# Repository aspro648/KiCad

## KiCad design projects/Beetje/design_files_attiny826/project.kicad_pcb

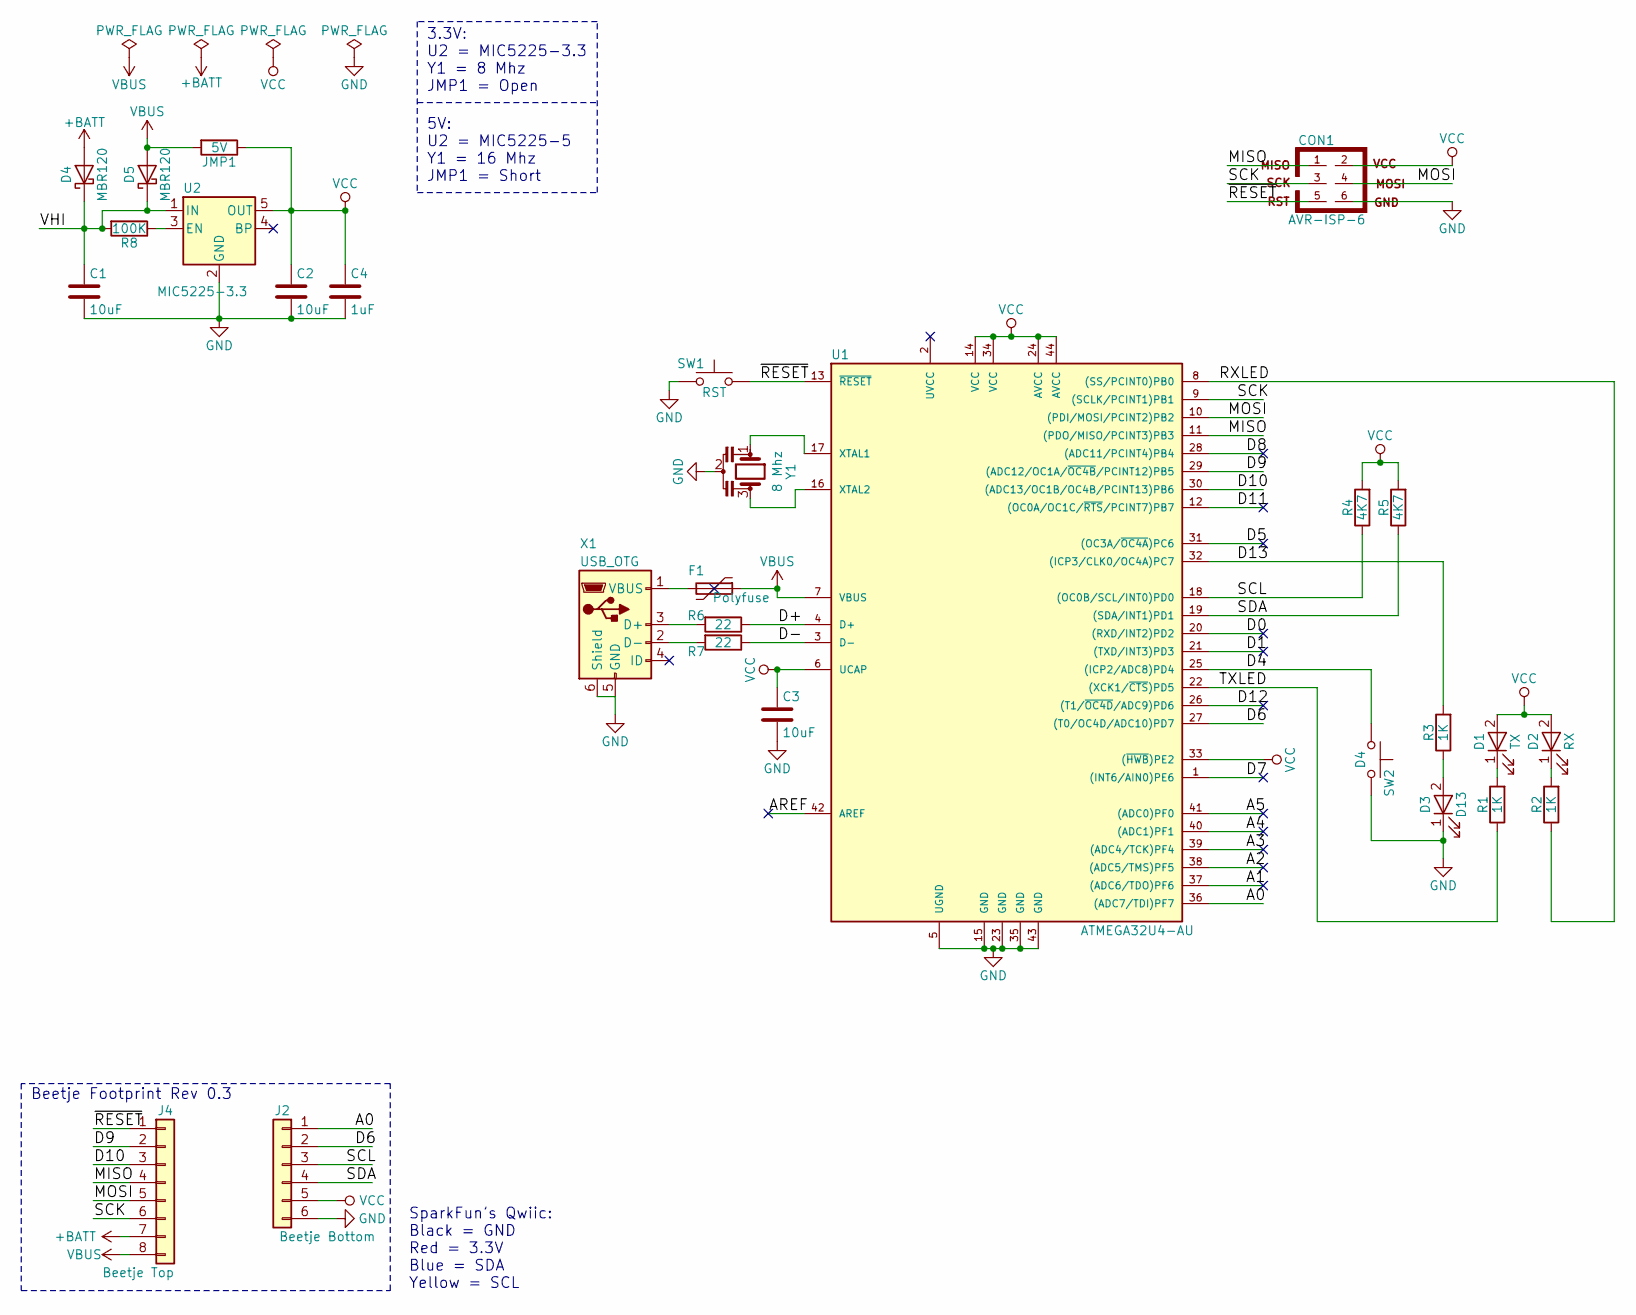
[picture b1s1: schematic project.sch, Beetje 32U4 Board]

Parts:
C1, C2, C3: 10uF; C_0805
C4: 1uF; C_0603
CON1: AVR-ISP-6; Pin_Header_Straight_2x03_Pitch2.54mm
D1: TX; LED_0603
D2: RX; LED_0603
D3: D13; LED_0603
D4, D5: MBR120; D_SOD-123F
F1: Polyfuse; R_1206
J2: Beetje Bottom; Beetje_Bottom
J4: Beetje Top; Beetje_Top
JMP1: 5V; Jumper
R1, R2, R3: 1K; R_0603
R4, R5: 4K7; R_0603
R6, R7: 22; R_0603
R8: 100K; R_0603
SW1: RST; EVQ-P7A
SW2: D4; EVQ-P7A
U1: ATMEGA32U4-AU; TQFP-44_10x10mm_Pitch0.8mm
U2: MIC5225-3.3; SOT-23-5
X1: USB_OTG; USB_Micro-B_Molex-105017-0001
Y1: 8 Mhz; Resonator_SMD_CTSC_1.3mmx3.2mm

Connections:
+BATT: D4.2 (A), J4.7
/A0: J2.1, U1.36 ((ADC7/TDI)PF7)
/A1: U1.37 ((ADC6/TDO)PF6)
/A2: U1.38 ((ADC5/TMS)PF5)
/A3: U1.39 ((ADC4/TCK)PF4)
/A4: U1.40 ((ADC1)PF1)
/A5: U1.41 ((ADC0)PF0)
/AREF: U1.42 (AREF)
/D0: U1.20 ((RXD/INT2)PD2)
/D1: U1.21 ((TXD/INT3)PD3)
/D4: SW2.1, U1.25 ((ICP2/ADC8)PD4)
/D5: U1.31 ((OC3A/~OC4A~)PC6)
/D6: J2.2, U1.27 ((T0/OC4D/ADC10)PD7)
/D7: U1.1 ((INT6/AIN0)PE6)
/D8: U1.28 ((ADC11/PCINT4)PB4)
/D9: J4.2, U1.29 ((ADC12/OC1A/~OC4B~/PCINT12)PB5)
/D10: J4.3, U1.30 ((ADC13/OC1B/OC4B/PCINT13)PB6)
/D11: U1.12 ((OC0A/OC1C/~RTS~/PCINT7)PB7)
/D12: U1.26 ((T1/~OC4D~/ADC9)PD6)
/D13: R3.2, U1.32 ((ICP3/CLK0/OC4A)PC7)
/D+: R6.1, U1.4 (D+)
/D-: R7.1, U1.3 (D-)
/MISO: CON1.1, J4.4, U1.11 ((PDO/MISO/PCINT3)PB3)
/MOSI: CON1.4, J4.5, U1.10 ((PDI/MOSI/PCINT2)PB2)
/RXLED: R2.1, U1.8 ((SS/PCINT0)PB0)
/SCK: CON1.3, J4.6, U1.9 ((SCLK/PCINT1)PB1)
/SCL: J2.3, R4.1, U1.18 ((OC0B/SCL/INT0)PD0)
/SDA: J2.4, R5.1, U1.19 ((SDA/INT1)PD1)
/TXLED: R1.1, U1.22 ((XCK1/~CTS~)PD5)
/VHI: C1.1, D4.1 (K), D5.1 (K), R8.2, U2.1 (IN)
/~RESET: CON1.5, J4.1, SW1.1, U1.13 (~RESET~)
GND: C1.2, C2.2, C3.2, C4.2, CON1.6, D3.1 (K), J2.6, SW1.2, SW2.2, U1.5 (UGND), U1.15 (GND), U1.23 (GND), U1.35 (GND), U1.43 (GND), U2.2 (GND), X1.5 (GND), X1.6 (Shield), Y1.2
unnamed: D1.1 (K), R1.2
unnamed: D2.1 (K), R2.2
unnamed: D3.2 (A), R3.1
unnamed: F1.2, X1.1 (VBUS)
unnamed: R6.2, X1.3 (D+)
unnamed: R7.2, X1.2 (D-)
unnamed: R8.1, U2.3 (EN)
unnamed: U1.16 (XTAL2), Y1.3
unnamed: U1.17 (XTAL1), Y1.1
VBUS: D5.2 (A), F1.1, J4.8, JMP1.2, U1.7 (VBUS)
VCC: C2.1, C3.1, C4.1, CON1.2, D1.2 (A), D2.2 (A), J2.5, JMP1.1, R4.2, R5.2, U1.6 (UCAP), U1.14 (VCC), U1.24 (AVCC), U1.33 ((~HWB~)PE2), U1.34 (VCC), U1.44 (AVCC), U2.5 (OUT)

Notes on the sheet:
3.3V: U2 = MIC5225-3.3 Y1 = 8 Mhz JMP1 = Open
5V: U2 = MIC5225-5 Y1 = 16 Mhz JMP1 = Short
Beetje Footprint Rev 0.3
SparkFun's Qwiic: Black = GND Red = 3.3V Blue = SDA Yellow = SCL

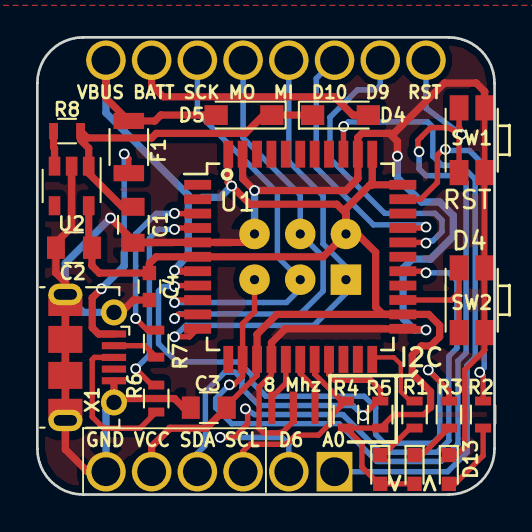
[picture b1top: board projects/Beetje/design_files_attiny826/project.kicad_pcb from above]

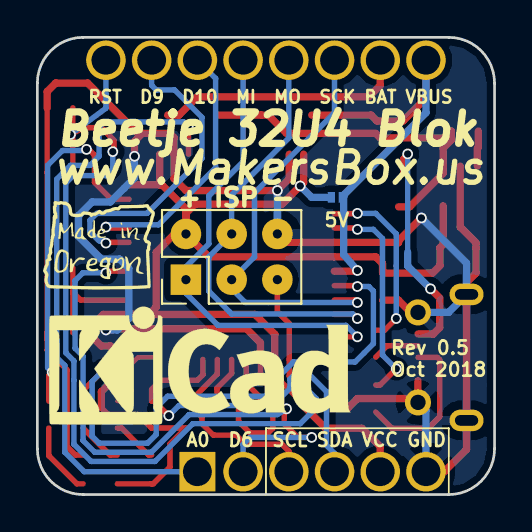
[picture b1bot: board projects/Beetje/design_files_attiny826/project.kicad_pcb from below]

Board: 2 copper layers, 25.4 x 25.4 mm, 29 parts (2 on the bottom side), 30 nets.

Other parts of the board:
VAL: MadeInOregonRev25

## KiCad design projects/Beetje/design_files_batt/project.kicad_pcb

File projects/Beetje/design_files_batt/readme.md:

Beetje Blok CR2032

Project website: https://hackaday.io/project/160638-beetje-bloks

Bill Of Materials
----------------
  
- 1 ea., Perfect Purple PCB from OSH Park, with not so perfect layout from [project.kicad_pcb](project.kicad_pcb) file.
- 1 ea. SMD Battery holder, Linx BAT-HLD-001, Digikey BAT-HLD-001-ND
- 1 ea. SMD SPST switch, C&K JS102011SAQN, Digikey 401-1999-1-ND
- 1 ea. CR2032 Battery, Panasonic CR2032, Digikey P189-ND (requires ground shipping, or buy locally).
- 1 ea., CONN HEADER .100" SNGL STR 40POS, https://www.digikey.com/short/jfcn42

License
----------------
[Attribution-ShareAlike 3.0 United States (CC BY-SA 3.0 US)](https://creativecommons.org/licenses/by-sa/3.0/us/)

You are free to:

- Share — copy and redistribute the material in any medium or format
- Adapt — remix, transform, and build upon the material

Under the following terms:

- Attribution — You must give appropriate credit, provide a link to the license, and indicate if changes were made. You may do so in any reasonable manner, but not in any way that suggests the licensor endorses you or your use.
- ShareAlike — If you remix, transform, or build upon the material, you must distribute your contributions under the same license as the original.

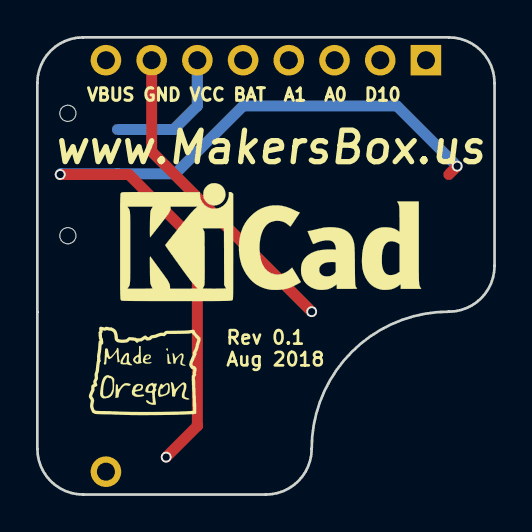
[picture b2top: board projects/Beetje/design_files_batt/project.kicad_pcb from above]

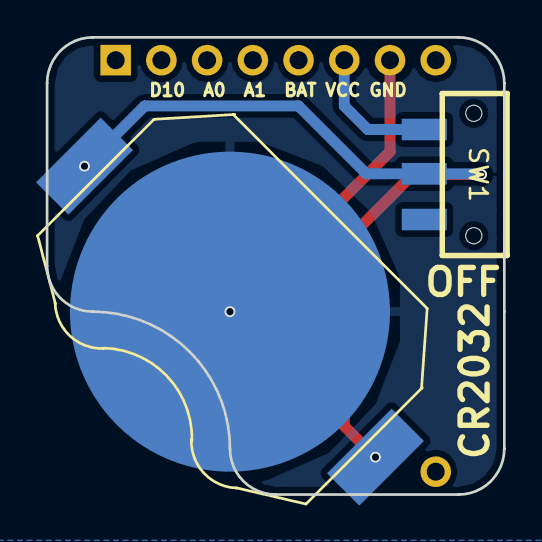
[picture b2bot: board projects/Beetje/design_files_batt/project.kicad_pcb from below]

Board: 2 copper layers, 25.4 x 25.4 mm, 5 parts (3 on the bottom side), 3 nets.

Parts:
BT1: Battery_Cell; BATT_CR2032_SMD
J2: Conn_01x06; Pin_Header_Straight_1x06_Pitch2.54mm
J4: Conn_01x08; Pin_Header_Straight_1x08_Pitch2.54mm
SW1: SW_SPDT; SPST_SMD
VAL: MadeInOregonRev25

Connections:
GND: BT1.2, J4.7
unnamed: BT1.1, SW1.2
VCC: J4.6, SW1.3

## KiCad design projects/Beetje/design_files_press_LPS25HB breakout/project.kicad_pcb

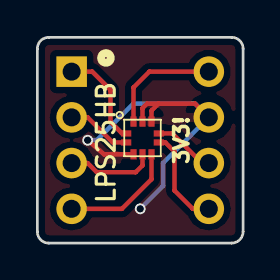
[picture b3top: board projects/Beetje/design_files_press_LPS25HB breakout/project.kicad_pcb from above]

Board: 2 copper layers, 11.4 x 11.4 mm, 3 parts (0 on the bottom side), 8 nets.

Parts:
J1: Conn_01x04_Left; Pin_Header_Left
J3: Conn_01x04_Right; Pin_Header_Right
U1: LPS25HB; ST_HLGA-10_2.5x2.5mm_P0.6mm_LayoutBorder3x2y

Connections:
GND: J3.8, U1.3, U1.8, U1.9
unnamed: J1.1, U1.1
unnamed: J1.2, U1.2
unnamed: J1.4, U1.4
unnamed: J1.5, U1.5
unnamed: J3.6, U1.6
unnamed: J3.7, U1.7
unnamed: J3.10, U1.10

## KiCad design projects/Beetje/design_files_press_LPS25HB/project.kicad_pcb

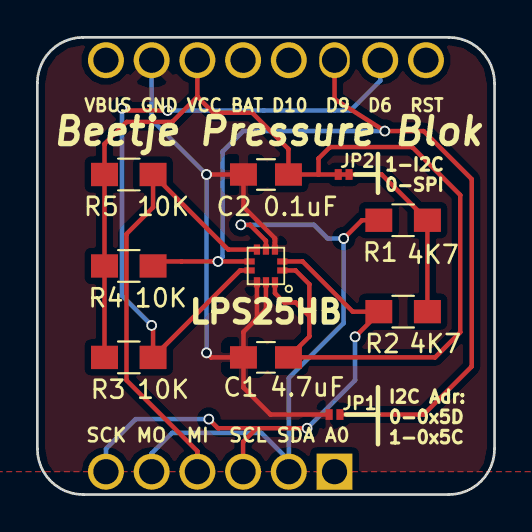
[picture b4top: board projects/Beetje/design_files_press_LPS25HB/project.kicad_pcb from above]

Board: 2 copper layers, 25.4 x 25.4 mm, 13 parts (0 on the bottom side), 7 nets.

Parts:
C1: 4.7uF; C_0805_HandSoldering
C2: 0.1uF; C_0805_HandSoldering
J2: Beetje_Bottom
J4: Beetje_Top
JP1, JP2: Jumper
R1, R2: 4K7; R_0805_HandSoldering
R3, R4, R5: 10K; R_0805_HandSoldering
U1: LPS25HB; ST_HLGA-10_2.5x2.5mm_P0.6mm_LayoutBorder3x2y
VAL: MadeInOregonRev25

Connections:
/INT_DRDY: J4.2, R3.1, U1.7
/SA0/MISO: J2.4, R5.1, U1.5
/SCL/SCLK: J2.3, J2.6, R2.1, U1.2
/SDA/MOSI: J2.2, J2.5, R1.1, U1.4
/~CS: J4.3, JP1.1, R4.1, U1.6
GND: C1.2, C2.2, J4.7, JP1.2, U1.3, U1.8, U1.9
VCC: C1.1, C2.1, J4.6, JP2.1, JP2.2, R1.2, R2.2, R3.2, R4.2, R5.2, U1.1, U1.10

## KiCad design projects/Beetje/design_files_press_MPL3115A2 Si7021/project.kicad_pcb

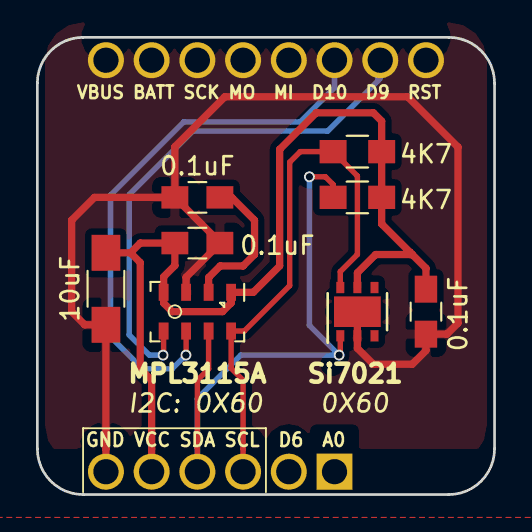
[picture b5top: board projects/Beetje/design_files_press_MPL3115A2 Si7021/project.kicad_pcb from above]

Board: 2 copper layers, 25.4 x 25.4 mm, 11 parts (0 on the bottom side), 7 nets.

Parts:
C1, C3, C4: 0.1uF; C_0805_HandSoldering
C2: 10uF; C_1206_HandSoldering
J2: Beetje_Bottom
J4: Beetje_Top
R1, R2: 4K7; R_0805_HandSoldering
U1: Si7021; DFN-6-1EP_3x3mm_Pitch0.95mm
U2: MPL3115A
VAL: MadeInOregonRev25

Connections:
/D9: J4.2, U2.5
/D10: J4.3, U2.6
/SCL: J2.3, R1.2, U1.6, U2.8
/SDA: J2.4, R2.2, U1.1, U2.7
GND: C1.2, C2.2, C3.2, C4.2, J2.6, U1.2, U1.7, U2.3
unnamed: C4.1, U2.2
VCC: C1.1, C2.1, C3.1, J2.5, R1.1, R2.1, U1.5, U2.1, U2.4

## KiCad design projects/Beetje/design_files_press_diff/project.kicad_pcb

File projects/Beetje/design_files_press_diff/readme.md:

Beetje LiPo Pressure Diff

Project website: https://hackaday.io/project/160638-beetje-bloks

Bill Of Materials
----------------
  
- 1 ea., Perfect Purple PCB from OSH Park, with not so perfect layout from [project.kicad_pcb](project.kicad_pcb) file.
- 1 ea., U1 NXP MP3V5010DP pressor sensor, https://www.digikey.com/short/jwjfhm (see options below)
- 1 ea., C1 CAP CER 1uF SMD 0805, https://www.digikey.com/short/jwjfn1
- 1 ea., C2 CAP CER 0.01uF SMD 0805, https://www.digikey.com/short/jwjf0c
- 1 ea., C3 CAP CER 470PF SMD 0805, https://www.digikey.com/short/jwjfrp

Optional (for I2C ADC)
-----------------

- 1 ea., MCP2031 I2C ADC SO23-5, https://www.digikey.com/short/jnq819
	- MCP3021A0T-E/OT: Extended, A0 Address
	- MCP3021A1T-E/OT: Extended, A1 Address
	- MCP3021A2T-E/OT: Extended, A2 Address
	- MCP3021A3T-E/OT: Extended, A3 Address
	- MCP3021A4T-E/OT: Extended, A4 Address
	- MCP3021A5T-E/OT: Extended, A5 Address
	- MCP3021A6T-E/OT: Extended, A6 Address
	- MCP3021A7T-IE/OT: Extended, A7 Address
- 1 ea., MCP2031 I2C ADC SO23-5, https://www.digikey.com/short/jnq819
- 2 ea., 4.7K OHM 0805 Resistors, 

(hopefully) Compatible Sesnsors:
-------------------
| PN          | Pressure Type | Operating Pressure                      | Voltage - Supply |
|-------------|---------------|-----------------------------------------|------------------|
| MP3V5004GP  | Vented Gauge  | 0.57 PSI (3.92 kPa)                     | 2.7 V ~ 3.3 V    |
| MP3V5010DP  | Differential  | 1.45 PSI (10 kPa)                       | 2.7 V ~ 3.3 V    | * Tested
| MP3V5050GP  | Vented Gauge  | 7.25 PSI (50 kPa)                       | 2.7 V ~ 3.3 V    |
| MP3V5050DP  | Differential  | 7.25 PSI (50 kPa)                       | 2.7 V ~ 3.3 V    |
| MPXV5004GP  | Vented Gauge  | 0.57 PSI (3.92 kPa)                     | 4.75 V ~ 5.25 V  |
| MPXV7002GP  | Compound      | ±0.29 PSI (±2 kPa)                      | 4.75 V ~ 5.25 V  |
| MPXV5050GP  | Vented Gauge  | 7.25 PSI (50 kPa)                       | 4.75 V ~ 5.25 V  |
| MPXV7007GP  | Compound      | ±1.02 PSI (±7 kPa)                      | 4.75 V ~ 5.25 V  |
| MPXV5010GP  | Vented Gauge  | 1.45 PSI (10 kPa)                       | 4.75 V ~ 5.25 V  |
| MPXAZ6115AP | Absolute      | 2.18 PSI ~ 16.68 PSI (15 kPa ~ 115 kPa) | 4.75 V ~ 5.25 V  |
| MPXV5100GP  | Vented Gauge  | 14.5 PSI (100 kPa)                      | 4.75 V ~ 5.25 V  |
| MPXV4006GP  | Vented Gauge  | 0.87 PSI (6 kPa)                        | 4.75 V ~ 5.25 V  |

Revisions
------------------
0.2 Swaped orientation to put connections on right to avoid USB connector.

License
----------------
[Attribution-ShareAlike 3.0 United States (CC BY-SA 3.0 US)](https://creativecommons.org/licenses/by-sa/3.0/us/)

You are free to:

- Share — copy and redistribute the material in any medium or format
- Adapt — remix, transform, and build upon the material

Under the following terms:

- Attribution — You must give appropriate credit, provide a link to the license, and indicate if changes were made. You may do so in any reasonable manner, but not in any way that suggests the licensor endorses you or your use.
- ShareAlike — If you remix, transform, or build upon the material, you must distribute your contributions under the same license as the original.

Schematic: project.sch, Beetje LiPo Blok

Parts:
C1: 1uF; C_0805
C2: 10nF; C_0805
C3: 470pF; C_0805
J2: Beetje_Bottom
J4: Beetje_Top
JP1, JP2: Jumper
R1, R2: 4K7; R_0805_HandSoldering
U1: MP3V5010; SSOP-8_2.95x2.8mm_Pitch0.65mm
U2: MCP3021; SOT-23-5

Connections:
+BATT: J4.7
/A0: C3.1, J2.1, JP1.1, JP1.2, JP2.1, U1.4 (VOUT)
/AIN: JP2.2, U2.3
/D6: J2.2
/D9: J4.2
/D10: J4.3
/MISO: J4.4
/MOSI: J4.5
/SCK: J4.6
/SCL: J2.3, R2.2, U2.5
/SDA: J2.4, R1.2, U2.4
/~RESET: J4.1
GND: C1.2, C2.2, C3.2, J2.6, U1.3 (GND), U2.2
VBUS: J4.8
VCC: C1.1, C2.1, J2.5, R1.1, R2.1, U1.2 (VSS), U2.1

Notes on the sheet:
Beetje Footprint Rev 0.3
Project website: https://hackaday.io/project/160638-beetje-bloks
Analog I2C JMP1 1 0 JMP2 0 1
I2C: 0x4D

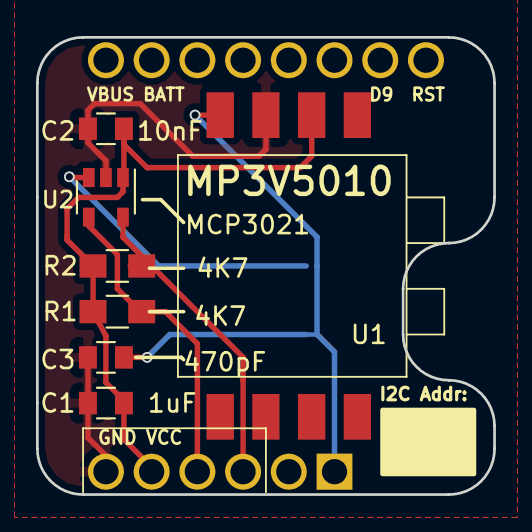
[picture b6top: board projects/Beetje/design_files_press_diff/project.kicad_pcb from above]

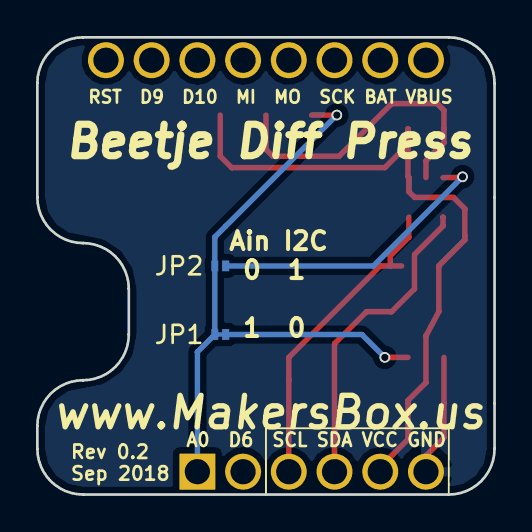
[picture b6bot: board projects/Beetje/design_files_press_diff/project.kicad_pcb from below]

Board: 2 copper layers, 25.4 x 25.4 mm, 11 parts (2 on the bottom side), 6 nets.

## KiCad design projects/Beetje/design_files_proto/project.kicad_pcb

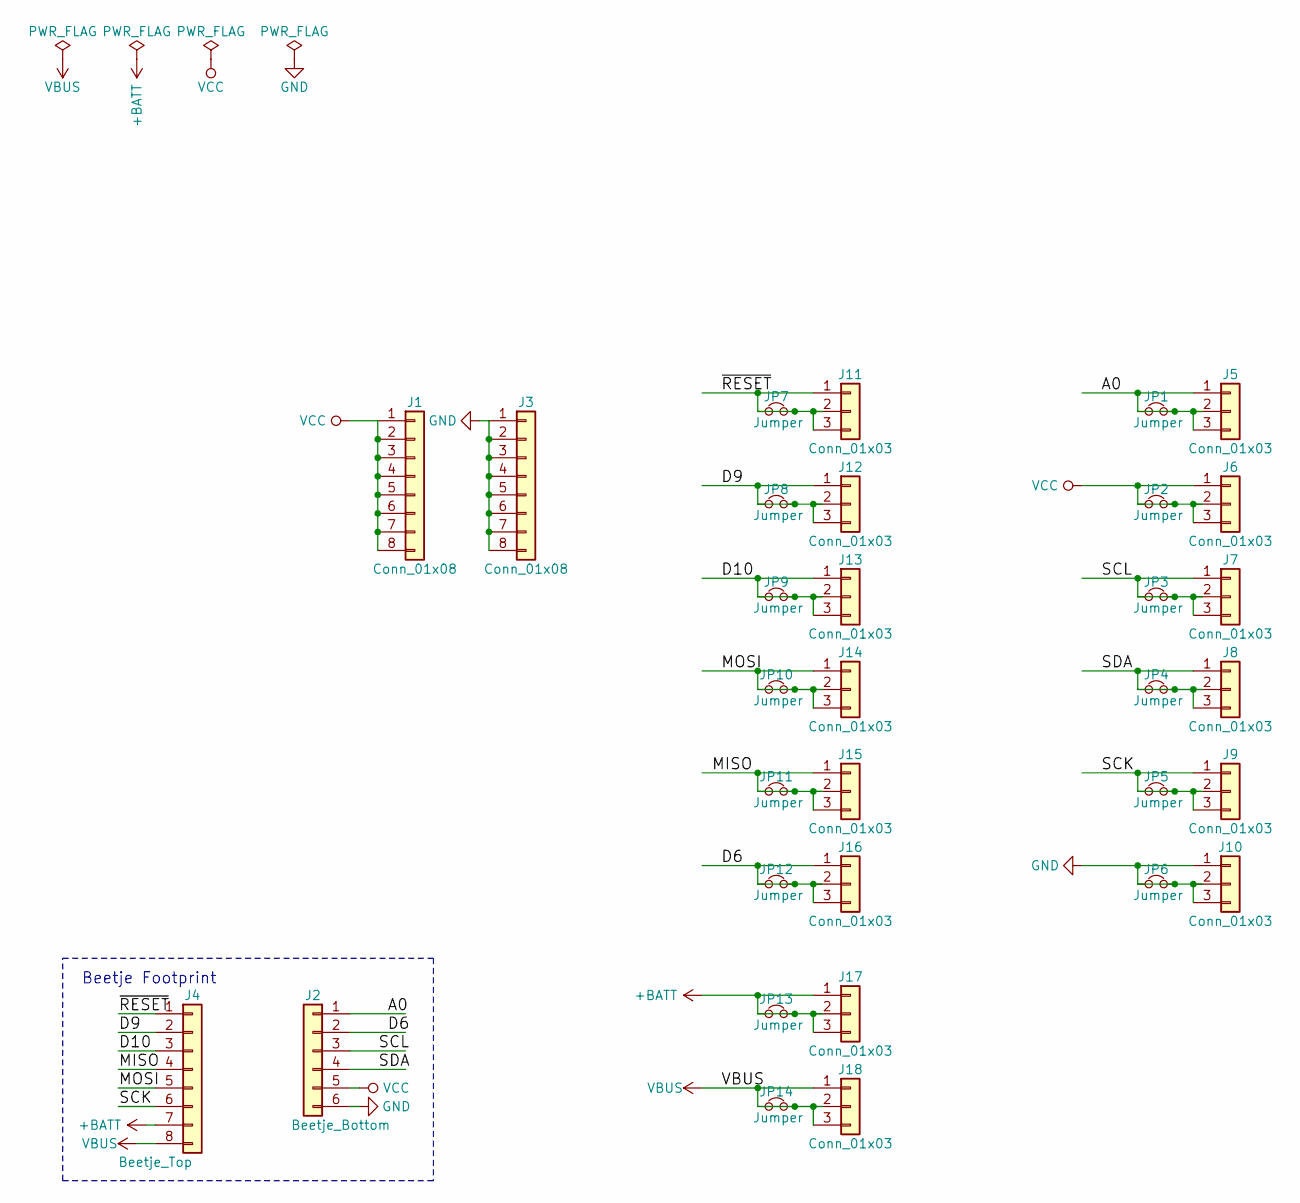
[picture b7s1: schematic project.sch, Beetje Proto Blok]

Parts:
J1, J3: Conn_01x08; Pin_Header_Straight_1x08_Pitch2.54mm
J2: Beetje_Bottom
J4: Beetje_Top
J5, J6, J7, J8, J9, J10, J11, J12, J13, J14, J15, J16, J17, J18: Conn_01x03; Pin_Header_1x03
JP1, JP2, JP3, JP4, JP5, JP6, JP7, JP8, JP9, JP10, JP11, JP12, JP13, JP14: Jumper

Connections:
+BATT: J4.7, J17.1, J17.2, J17.3, JP13.1
/A0: J2.1, J5.1, J5.2, J5.3, JP1.1
/D6: J2.2, J16.1, J16.2, J16.3, JP12.1
/D9: J4.2, J12.1, J12.2, J12.3, JP8.1
/D10: J4.3, J13.1, J13.2, J13.3, JP9.1
/MISO: J4.4, J15.1, J15.2, J15.3, JP11.1
/MOSI: J4.5, J14.1, J14.2, J14.3, JP10.1
/SCK: J4.6, J9.1, J9.2, J9.3, JP5.1
/SCL: J2.3, J7.1, J7.2, J7.3, JP3.1
/SDA: J2.4, J8.1, J8.2, J8.3, JP4.1
/~RESET: J4.1, J11.1, J11.2, J11.3, JP7.1
GND: J2.6, J3.1, J3.2, J3.3, J3.4, J3.5, J3.6, J3.7, J3.8, J10.1, J10.2, J10.3, JP6.1
VBUS: J4.8, J18.1, J18.2, J18.3, JP14.1
VCC: J1.1, J1.2, J1.3, J1.4, J1.5, J1.6, J1.7, J1.8, J2.5, J6.1, J6.2, J6.3, JP2.1

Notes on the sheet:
Beetje Footprint

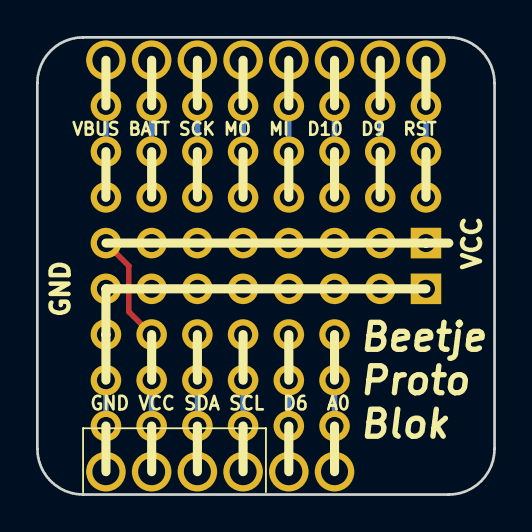
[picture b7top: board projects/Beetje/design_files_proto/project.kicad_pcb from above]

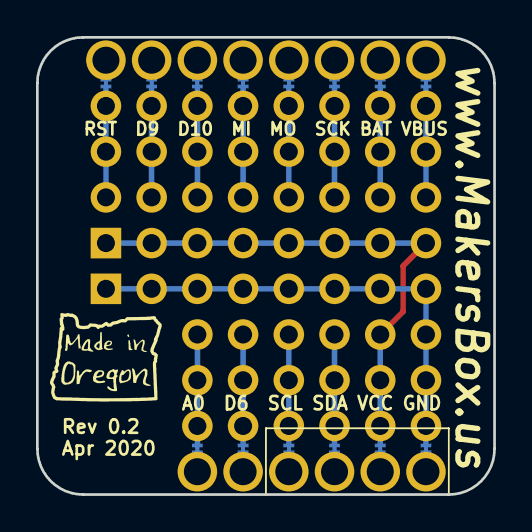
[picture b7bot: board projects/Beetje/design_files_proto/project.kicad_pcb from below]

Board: 2 copper layers, 25.4 x 25.4 mm, 33 parts (14 on the bottom side), 14 nets.

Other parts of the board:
VAL: MadeInOregonRev25

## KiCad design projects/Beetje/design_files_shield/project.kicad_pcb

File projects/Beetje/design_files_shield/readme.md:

Beetje Blok 32U4 Rev 0.0

https://rheingoldheavy.com/arduino-from-scratch-part-5-selecting-comparator-parts/

Based on Adafruit's [ItsyBitsy](https://learn.adafruit.com/introducting-itsy-bitsy-32u4) and SparkFun's [Pro Micro](https://www.sparkfun.com/products/12587) 3.3V/8Mhz versions.

Project page on [Hack-A-Day](https://hackaday.io/project/160638-beetje-bloks).

This is the first "dev blok" for this proof-of-concept project.  It is a KiCad mash-up of Adafruit's [ItsyBity](https://learn.adafruit.com/introducting-itsy-bitsy-32u4) and SparkFun's [Pro Micro](https://www.sparkfun.com/products/12587), jammed into Hack-A-Day's [Once Square Inch Scheme](https://hackaday.io/project/7813-the-square-inch-project) ("HADOSIS").

Bill Of Materials
----------------
  
- 1 ea., Perfect Purple PCB from OSH Park, with not so perfect kicad.pcb file.
- 1 ea., U1 IC REG LINEAR 3.3V 150MA SOT23-5, LP2985-33DBVRG4, https://www.digikey.com/short/j29pqr
- 1 ea., U2 IC OPAMP GP 1MHZ RRO 8VSSOP, LMV358IDGKR, https://www.digikey.com/short/j29pj7
- 1 ea., U4 ATMEGA32U4-AU, IC MCU 8BIT 32KB FLASH 44TQFP, https://www.digikey.com/short/jb25pc
- 1 ea., U3 IC REG LINEAR 5V 1A SOT223 NCP1117ST50T3G, https://www.digikey.com/short/j29pqc
- 1 ea., Q1 MOSFET P-CH 20V 2A SSOT3, FDN340P, https://www.digikey.com/short/j29ppj

- 1 ea., Y1 CER RES 16.0000MHZ 15PF SMD, CSTCE16M0V53-R0, https://www.digikey.com/short/j2b9cm
- 2 ea., C3, C6, C7 CAP CER 10UF 25V X7R 1206, https://www.digikey.com/short/j29pwm
- 2 ea., C1, C5 CAP CER 1UF SMD 0805
- 1 ea., C4 CAP CER 0.1UF SMD 0805
- 1 ea., C2 CAP CER 22pF SMD 0805

- F1, PTC 1206, Bel 0ZCJ0025AF2E, https://www.digikey.com/short/jfcbc8
- 2 ea., RV1, RV2 VARISTOR 	VARISTOR 10.8V 40A 0805, https://www.digikey.com/product-detail/en/VCUG080050L1DP/478-5584-1-ND/2048376/?itemSeq=271121312
- 4 ea., R1-R4 Resistor 1K OHM SMD 0805
- 2 ea., R5, R8 Resistor 10K OHM SMD 0805
- 2 ea., R6, R7 Resistor 22 OHM SMD 0805
- 1 ea., R9 Resistor 1M OHM SMD 0603
- 4 ea., D1-D4 SMD LED 0805

- 1 ea., SW1 SWITCH TACTILE SPST-NO 0.05A 12V, PTS645SK50SMTR92 LFS, https://www.digikey.com/short/j29hvc
- 1 ea., X3, CONN RCPT MICRO USB R/A SMD, Molex 1050170001, https://www.digikey.com/short/jb2205
- 1 ea., J1 Barrel Jack, https://www.digikey.com/short/j2fz43
- 1 ea., 6-Pin header
- 2 ea., 8-Pin header
- 1 ea., 10-Pin header

License
----------------
[Attribution-ShareAlike 3.0 United States (CC BY-SA 3.0 US)](https://creativecommons.org/licenses/by-sa/3.0/us/)

You are free to:

- Share — copy and redistribute the material in any medium or format
- Adapt — remix, transform, and build upon the material

Under the following terms:

- Attribution — You must give appropriate credit, provide a link to the license, and indicate if changes were made. You may do so in any reasonable manner, but not in any way that suggests the licensor endorses you or your use.
- ShareAlike — If you remix, transform, or build upon the material, you must distribute your contributions under the same license as the original.

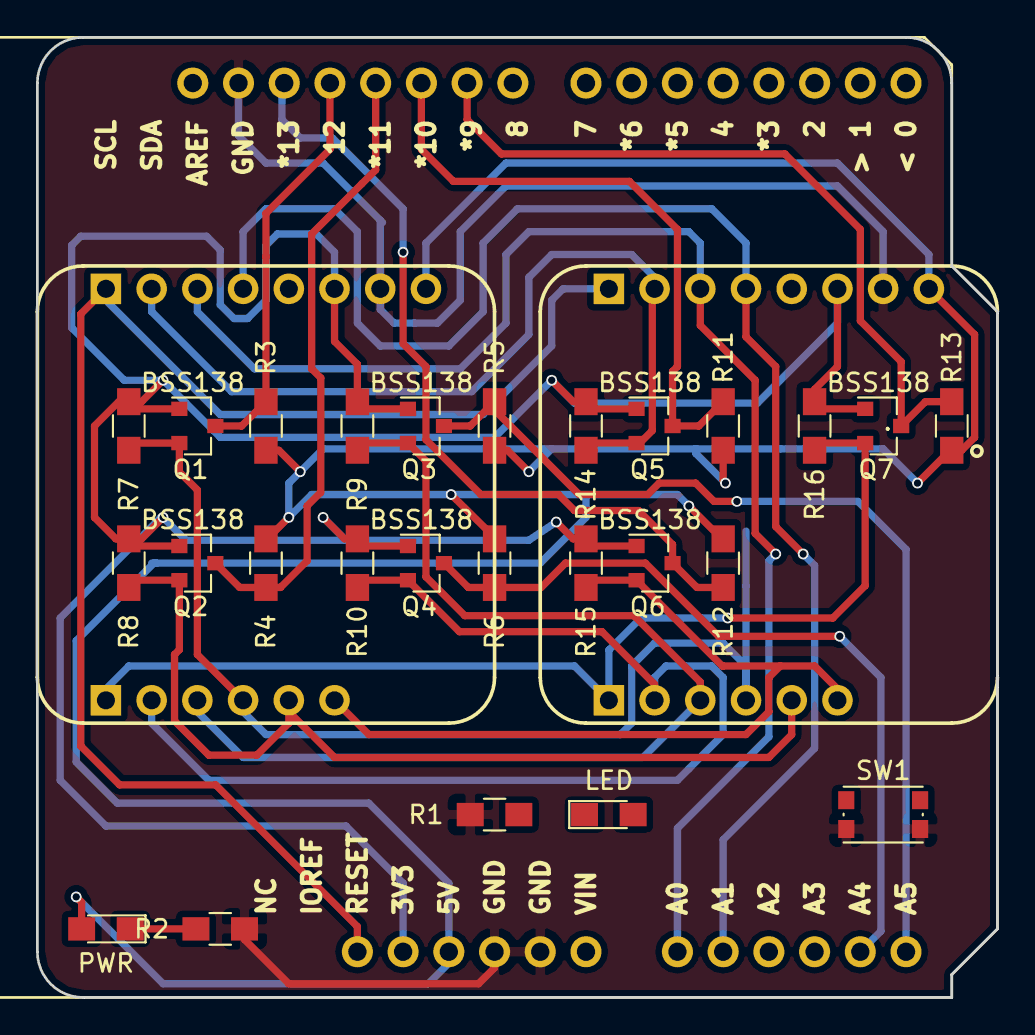
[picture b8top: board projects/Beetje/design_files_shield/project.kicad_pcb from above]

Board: 2 copper layers, 53.3 x 53.3 mm, 32 parts (0 on the bottom side), 22 nets.

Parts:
D1: LED; LED_0805_HandSoldering
D2: PWR; LED_0805_HandSoldering
J2, J2#2: Beetje_Bottom; Pin_Header_Straight_1x06_Pitch2.54mm
J4, J4#2: Beetje_Top; Pin_Header_Straight_1x08_Pitch2.54mm
Q1, Q2, Q3, Q4, Q5, Q6, Q7: BSS138; SOT-23
R1, R2: 1K; R_0805_HandSoldering
R3, R4, R5, R6, R7, R8, R9, R10, R11, R12, R13, R14, R15, R16: 10K; R_0805_HandSoldering
SW1: SW_Push; SW_SPST_KMR2
VAL: MadeInOregonRev25
XA1: Arduino_Leonardo_Shield

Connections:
+3V3: J4.6, J4#2.6, Q1.1, Q2.1, Q3.1, Q4.1, Q5.1, Q6.1, Q7.1, R7.2, R8.2, R9.2, R10.2, R14.2, R15.2, R16.2, XA1.3V3
+5V: D2.2, J4.8, J4#2.8, R3.2, R4.2, R5.2, R6.2, R11.2, R12.2, R13.2, XA1.5V1
/A0: J4.3, J4#2.3, XA1.A0
/A1: J4.4, J4#2.4, XA1.A1
/D9: J2.1, J2#2.1, Q7.2, R16.1
/D9_5V: Q7.3, R13.1, XA1.D9
/D10: J4.2, J4#2.2, Q5.2, R14.1
/D10_5V: Q5.3, R11.1, XA1.D10
/MISO: J2.4, J2#2.4, Q1.2, R7.1
/MISO_5V: Q1.3, R3.1, XA1.D12
/MOSI: J2.5, J2#2.5, Q2.2, R8.1
/MOSI_5V: Q2.3, R4.1, XA1.D11
/SCK: J2.6, J2#2.6, Q6.2, R15.1
/SCK_5V: Q6.3, R12.1, XA1.D13
/SCL: J2.3, J2#2.3, Q3.2, R9.1
/SCL_5V: Q3.3, R5.1, XA1.A5
/SDA: J2.2, J2#2.2, Q4.2, R10.1
/SDA_5V: Q4.3, R6.1, XA1.A4
/~RESET: J4.1, J4#2.1, XA1.RST1
GND: J4.7, J4#2.7, R1.1, R2.2, SW1.2, XA1.GND1, XA1.GND2, XA1.GND3
unnamed: D1.1, R1.2
unnamed: D2.1, R2.1
